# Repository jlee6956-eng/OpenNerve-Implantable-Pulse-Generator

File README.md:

# OpenNerve-Implantable-Pulse-Generator
Source files for the OpenNerve implantable pulse generator (IPG), charger, and user interface software

## Overview

The OpenNerve IPG is designed to enable researchers to develop novel therapies in the neuromodulation and bioelectronic medicine spaces. It is currently being used by a number of groups for acute and chronic preclinical studies, with plan to transition to clinical studies when ready.The IPG is capable of providing current-based bipolar electrical stimulation, measuring biosignals using multiple analog front ends (AFEs), and connecting with third-party sensors via an in-body I2C network. It communicates with a user controller over Bluetooth Low Energy (BLE) and can be easily configured to be rechargeable over inductive link. All source files are released under the CC-BY 4.0 open source copyright license, which requires attribution but allows their use for closed-source and commercial applications.

## Electronics
Two versions of the printed circuit board inside OpenNerve have been designed and manufactured. The [Gen1 PCBA](https://github.com/CARSSCenter/OpenNerve-Implantable-Pulse-Generator/Gen1%20PCBA) has eight pseudo-independent monopolar stimulation channels (configurable as four bipolar channels), two differential biosignal amplifiers for recording ECG, EMG, or eCAPS, and an I2C port for connection to an accelerometer or other in-body digital sensors. The [Gen2 PCBA](https://github.com/CARSSCenter/OpenNerve-Implantable-Pulse-Generator/tree/main/Gen2%20PCBA) has two fully independent bipolar stimulation channels capable of square wave stimulation up to 1200 Hz or low frequency sine wave stimulation, four configurable analog front ends, and an I2C port. See below for electrical specifications for the Gen2 IPG (square wave stimulation and analog front-ends).

## Firmware
OpenNerve contains two microcontrollers: an nRF52810 which controlls BLE communication (referred to as "BLE"), and an STM32 which controls most other functions (referred to as "MCU"). BLE firmware is the same for both Gen1 and Gen2 PCBAs and can be found [here](https://github.com/CARSSCenter/OpenNerve-Implantable-Pulse-Generator/tree/main/FW-BLE). Instructions for programming a new board can be found in the [BLE Flashing Guide](https://github.com/CARSSCenter/OpenNerve-Implantable-Pulse-Generator/blob/main/Docs/BLE-Flashing-Guide.md) under Docs. MCU firmware is different for Gen1 and Gen2 IPGs; the source code and hex files for each board's MCU firmware can be found in their respective folders, and instructions for compiling and flashing can be found at [MCU Flashing Guide](https://github.com/CARSSCenter/OpenNerve-Implantable-Pulse-Generator/blob/main/Docs/MCU-Flashing-Guide.md).

## Software
A Windows application has been written in VSCode to control OpenNerve's functions and download/save measurements. The source code for this app can be found in the [OpenNerve Windows App repo](https://github.com/CARSSCenter/OpenNerve-Windows-App). To communicate with OpenNerve using this app requires an encryption private key. To get the key used for the open-source builds of MCU2 firmware please reach out to carss@usc.edu. There are also instructions included [here](https://github.com/CARSSCenter/OpenNerve-Windows-App/blob/main/encryption-instructions.md) on how to create your own encryption keys and firmware build.

An Android app is also under development for communication and control with OpenNerve. Prototype code for this app can be found [here](https://github.com/CARSSCenter/OpenNerve-Android-App).

## Wireless charger
The OpenNerve IPG can be charged inductively using the [OpenNerve Charger](https://github.com/CARSSCenter/OpenNerve-Charger).

## Contributors
The OpenNerve IPG has been designed and manufactured in partnership with a number of contributors from the academic and private sectors, all of whom are committed to open source neurotech and lowering the barrier to developing new therapies. See below for a list of contributing organizations (last updated 22/01/2026).
* [Biomedical Microsystems Lab, University of Southern California](https://biomems.usc.edu/) - lead the larger CARSS center, set up and maintains open source resources, performs integration testing, software development, and preclinical studies
* [Med-Ally LLC](https://med-ally.com/) - designed the hermetic enclosure for OpenNerve, and provides final assembly services for chronic studies
* [Medipace Inc](https://www.medipaceinc.com/) - Manages electronics and firmware development, performs software development
* [Focus Uy](https://focus.uy/) - Designed the printed circuit board for OpenNerve IPG and charger
* [CoForce Ltd.](https://www.coforcemed.com/) - Peformed firmware development for OpenNerve
* [Veronica Rosado.](https://www.linkedin.com/in/veronica-rosado-silva/) - Developed Sine Wave Generator tool for OpenNerve
* [Julian Lee](https://www.linkedin.com/in/julian-lee-t/) - Worked on sine wave generator

Funding for OpenNerve has been provided by the US National Institutes of Health's SPARC program # [1U41NS129514](https://reporter.nih.gov/project-details/10557000) as well as by the US National Science Foundation's POSE Phase 1 program # [2449357](https://www.nsf.gov/awardsearch/show-award?AWD_ID=2449357). 

# Disclaimer

The contents of this repository are subject to revision. No representation or warranty, express or implied, is provided in relation to the accuracy, correctness, completeness, or reliability of the information, opinions, or conclusions expressed in this repository.

The contents of this repository (the “Materials”) are experimental in nature and should be used with prudence and appropriate caution. Any use is voluntary and at your own risk.

The Materials are made available “as is” by USC (the University of Southern California and its trustees, directors, officers, employees, faculty, students, agents, affiliated organizations and their insurance carriers, if any), its collaborators Med-Ally LLC and Medipace Inc., and any other contributors to this repository (collectively, “Providers”). Providers expressly disclaim all warranties, express or implied, arising in connection with the Materials, or arising out of a course of performance, dealing, or trade usage, including, without limitation, any warranties of title, noninfringement, merchantability, or fitness for a particular purpose.

Any user of the Materials agrees to forever indemnify, defend, and hold harmless Providers from and against, and to waive any and all claims against Providers for any and all claims, suits, demands, liability, loss or damage whatsoever, including attorneys' fees, whether direct or consequential, on account of any loss, injury, death or damage to any person or (including without limitation all agents and employees of Providers and all property owned by, leased to or used by either Providers) or on account of any loss or damages to business or reputations or privacy of any persons, arising in whole or in part in any way from use of the Materials or in any way connected therewith or in any way related thereto.

The Materials, any related materials, and all intellectual property therein, are owned by Providers.

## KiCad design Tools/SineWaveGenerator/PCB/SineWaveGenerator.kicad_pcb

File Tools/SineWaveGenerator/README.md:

# SineWaveGeneratorDev
Development for sine wave generator

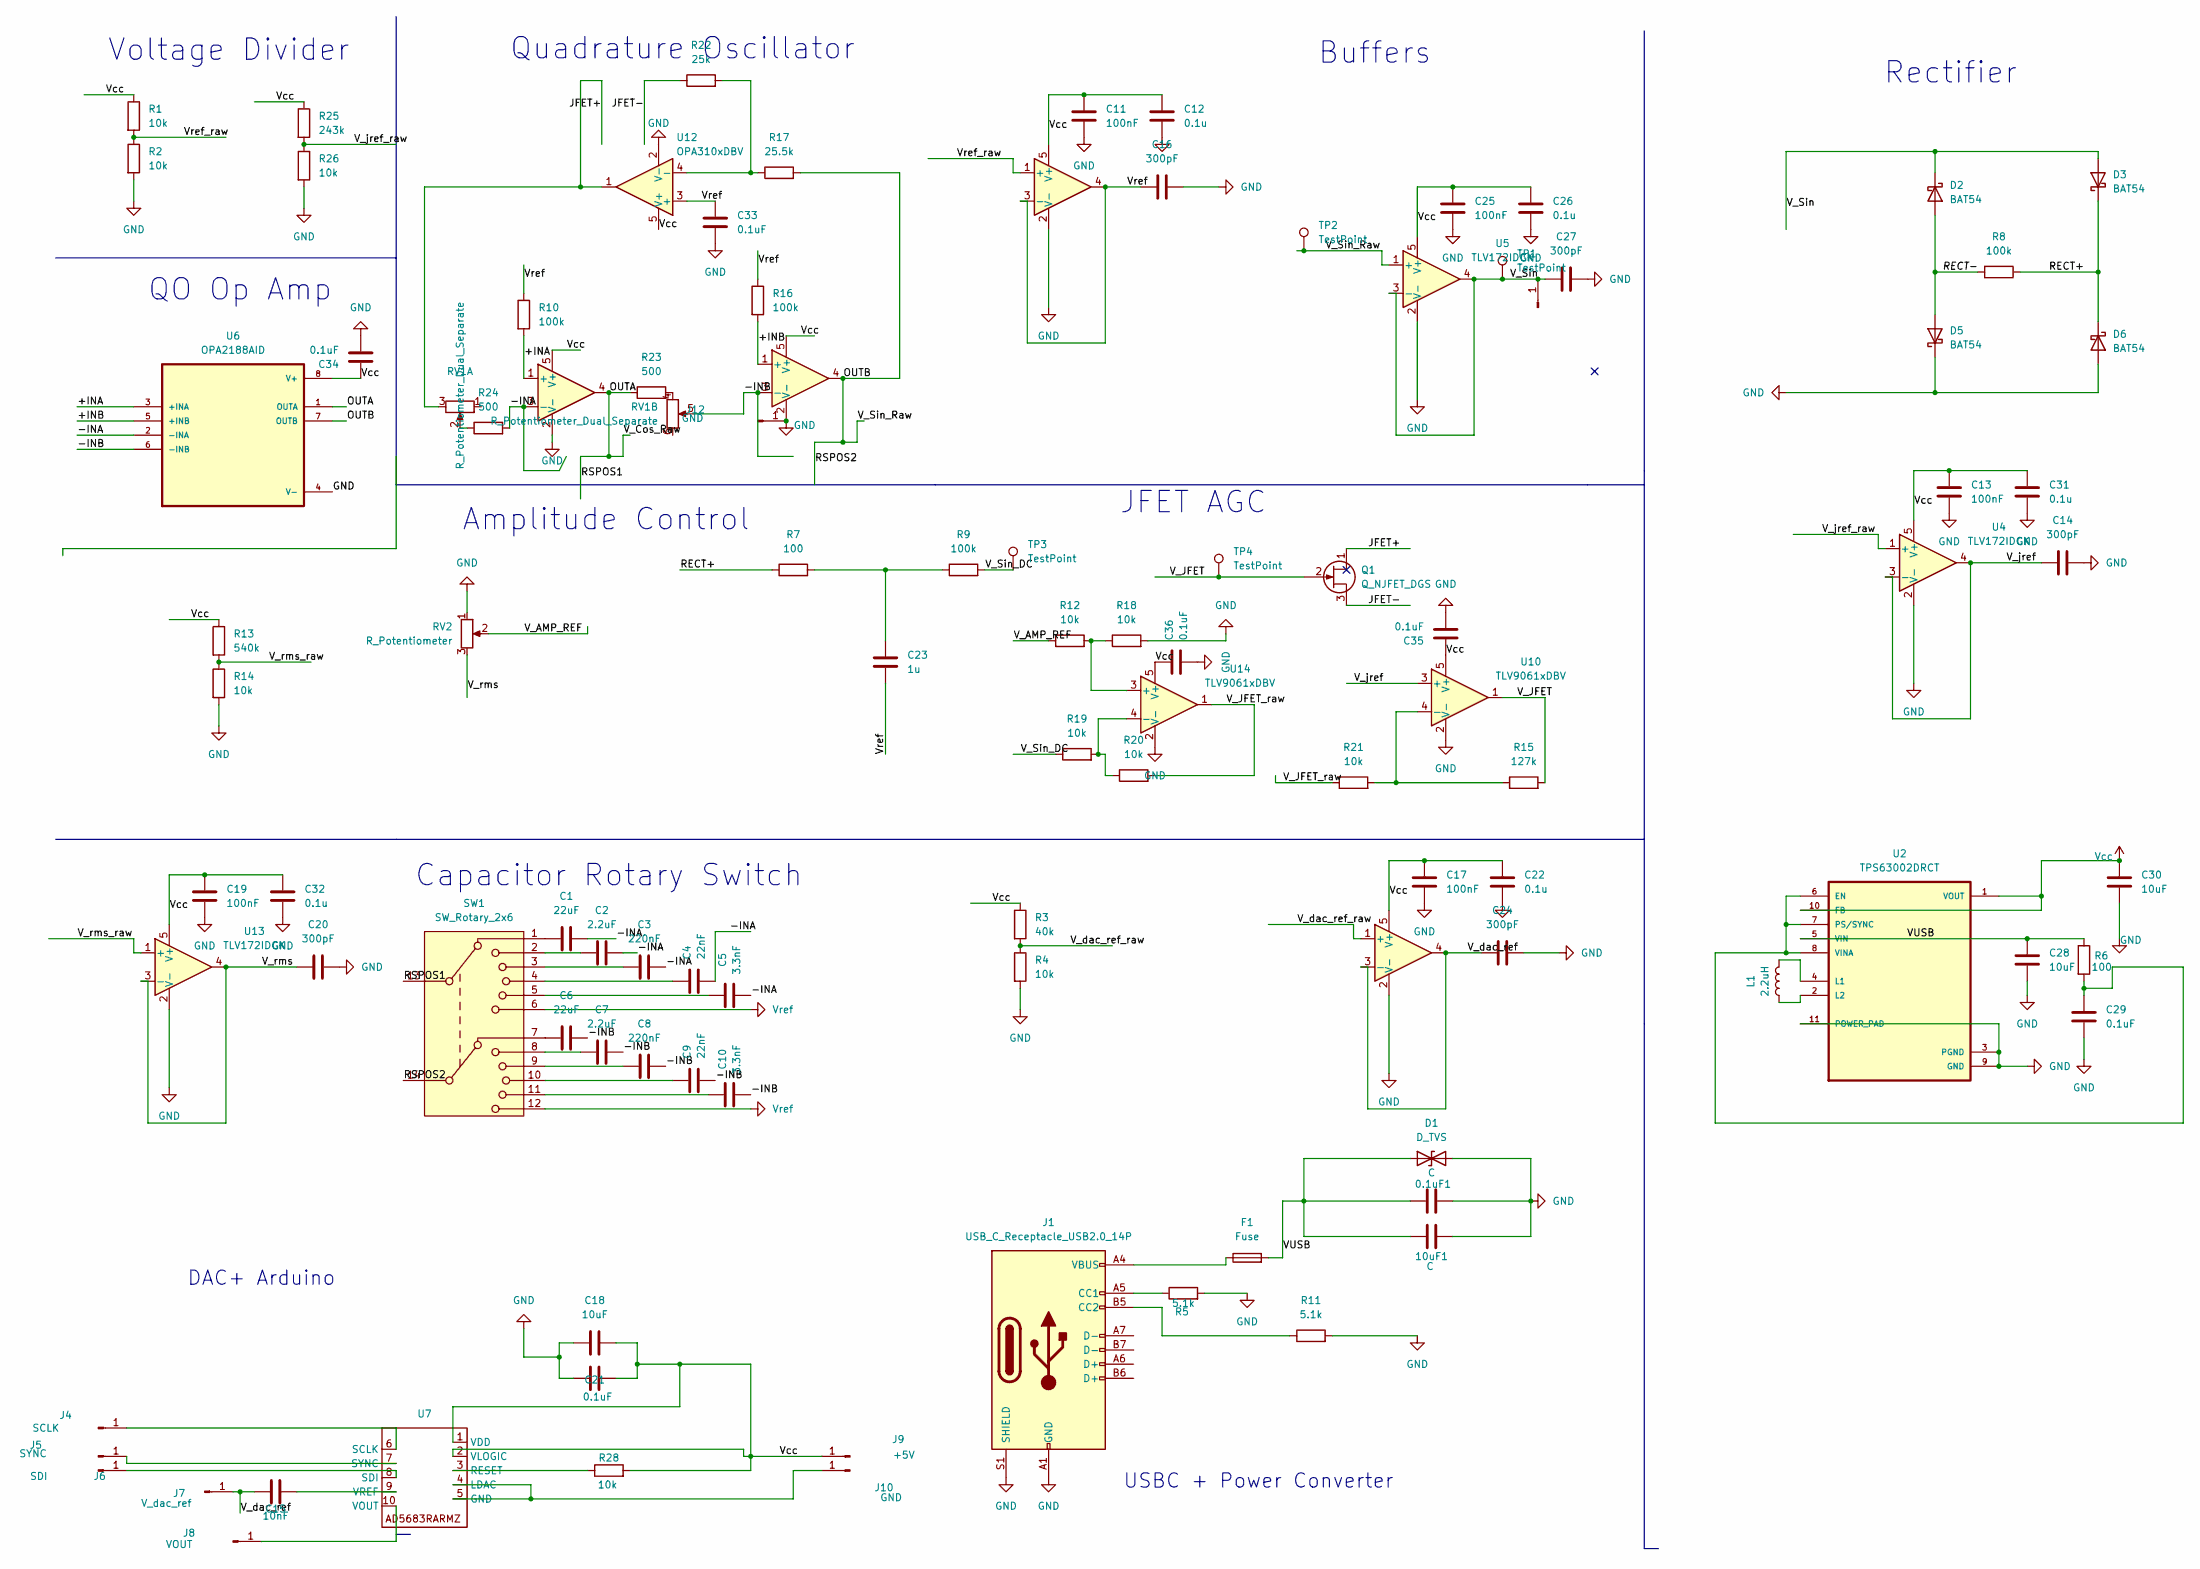
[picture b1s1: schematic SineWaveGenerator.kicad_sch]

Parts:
0.1uF1, 10uF1: C; C_0805_2012Metric_Pad1.18x1.45mm_HandSolder
C1, C6: 22uF; C_0805_2012Metric_Pad1.18x1.45mm_HandSolder
C2, C7: 2.2uF; C_0805_2012Metric_Pad1.18x1.45mm_HandSolder
C3, C8: 220nF; C_0805_2012Metric_Pad1.18x1.45mm_HandSolder
C4, C9: 22nF; C_0805_2012Metric_Pad1.18x1.45mm_HandSolder
C5, C10: 3.3nF; C_0805_2012Metric_Pad1.18x1.45mm_HandSolder
C11, C13, C17, C19, C25: 100nF; C_0805_2012Metric_Pad1.18x1.45mm_HandSolder
C12, C22, C26, C31, C32: 0.1u; C_0805_2012Metric_Pad1.18x1.45mm_HandSolder
C14, C16, C20, C24, C27: 300pF; C_0805_2012Metric_Pad1.18x1.45mm_HandSolder
C15: 10nF; C_0805_2012Metric_Pad1.18x1.45mm_HandSolder
C18, C28, C30: 10uF; C_0805_2012Metric_Pad1.18x1.45mm_HandSolder
C21, C29, C33, C34, C35, C36: 0.1uF; C_0805_2012Metric_Pad1.18x1.45mm_HandSolder
C23: 1u; C_0603_1608Metric_Pad1.08x0.95mm_HandSolder
D1: D_TVS; D_SOD-323_HandSoldering
D2, D3, D5, D6: BAT54; D_0805_2012Metric_Pad1.15x1.40mm_HandSolder
F1: Fuse; Fuse_0805_2012Metric
J1: USB_C_Receptacle_USB2.0_14P; USB_C_Receptacle_HRO_TYPE-C-31-M-12
J4: SCLK; PinHeader_1x01_P2.54mm_Vertical
J5: SYNC; PinHeader_1x01_P2.54mm_Vertical
J6: SDI; PinHeader_1x01_P2.54mm_Vertical
J7: V_dac_ref; PinHeader_1x01_P2.54mm_Vertical
J8: VOUT; PinHeader_1x01_P2.54mm_Vertical
J9: +5V; PinHeader_1x01_P2.54mm_Vertical
J10, J12: GND; PinHeader_1x01_P2.54mm_Vertical
J11: Out_Sin; PinHeader_1x01_P2.54mm_Vertical
L1: 2.2uH; L_Coilcraft_LPS3010
Q1: Q_NJFET_DGS; TRANS_J201
R1, R2, R4, R12, R14, R18, R19, R20, R21, R26, R28: 10k; R_0805_2012Metric_Pad1.20x1.40mm_HandSolder
R3: 40k; R_0805_2012Metric_Pad1.20x1.40mm_HandSolder
R5, R11: 5.1k; R_0805_2012Metric_Pad1.20x1.40mm_HandSolder
R6, R7: 100; R_0805_2012Metric_Pad1.20x1.40mm_HandSolder
R8, R9, R10, R16: 100k; R_0805_2012Metric_Pad1.20x1.40mm_HandSolder
R13: 540k; R_0805_2012Metric_Pad1.20x1.40mm_HandSolder
R15: 127k; R_0805_2012Metric_Pad1.20x1.40mm_HandSolder
R17: 25.5k; R_0805_2012Metric_Pad1.20x1.40mm_HandSolder
R22: 25k; R_0805_2012Metric_Pad1.20x1.40mm_HandSolder
R23, R24: 500; R_0805_2012Metric_Pad1.20x1.40mm_HandSolder
R25: 243k; R_0805_2012Metric_Pad1.20x1.40mm_HandSolder
RV1: R_Potentiometer_Dual_Separate; DUALGANG_fixed
RV2: R_Potentiometer; BOURNS_POT
SW1: SW_Rotary_2x6; SW_CK1050
TP1, TP2, TP3, TP4: TestPoint; TestPoint_Pad_D1.0mm
U2: TPS63002DRCT; VREG_V62_16624-01YE
U4, U5, U8, U11, U13, U15, U16: TLV172IDCK; SOT-353_SC-70-5
U6: OPA2188AID; SOIC127P599X175-8N
U7: MSOP-10_3x3mm_P0.5mm
U10, U14: TLV9061xDBV; SOT-23-5
U12: OPA310xDBV; SOT-23-5

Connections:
/+INA: R10.2, U6.3 (+INA), U8.1 (+)
/+INB: R16.2, U6.5 (+INB), U11.1 (+)
/-INA: C1.2, C2.2, C3.2, C4.2, C5.2, R24.2, U6.2 (-INA), U8.3 (-)
/-INB: C6.2, C7.2, C8.2, C9.2, C10.2, RV1.5, U6.6 (-INB), U11.3 (-)
/JFET+: Q1.1 (D), RV1.3, U12.1
/JFET-: Q1.3 (S), R22.1
/OUTA: R23.1, SW1.13, U6.1 (OUTA), U8.4
/OUTB: R17.2, SW1.14, TP2.1 (1_1), U5.1 (+), U6.7 (OUTB), U11.4
/RECT+: D3.1 (K), D6.1 (K), R7.1, R8.1
/RECT-: D2.2 (A), D5.2 (A), R8.2
/VUSB: 0.1uF1.1, 10uF1.1, C28.1, D1.1 (A1), F1.2, R6.1, U2.5 (VIN)
/V_AMP_REF: R12.1, RV2.2
/V_JFET: Q1.2 (G), R15.2, TP4.1 (1_1), U10.1
/V_JFET_raw: R20.2, R21.1, U14.1
/V_Sin: C27.1, D2.1 (K), D3.2 (A), J11.1 (Pin_1_1), TP1.1 (1_1), U5.3 (-), U5.4
/V_Sin_DC: R9.2, R19.1, TP3.1 (1_1)
/V_dac_ref: C15.1, C24.1, J7.1 (Pin_1_1), U16.3 (-), U16.4
/V_dac_ref_raw: R3.2, R4.1, U16.1 (+)
/V_jref: C14.1, U4.3 (-), U4.4, U10.3 (+)
/V_jref_raw: R25.2, R26.1, U4.1 (+)
/V_rms: C20.1, RV2.3, U13.3 (-), U13.4
/V_rms_raw: R13.2, R14.1, U13.1 (+)
/Vref_raw: R1.2, R2.1, U15.1 (+)
GND: 0.1uF1.2, 10uF1.2, C11.2, C12.2, C13.1, C14.2, C16.2, C17.2, C18.1, C19.1, C20.2, C21.1, C22.2, C24.2, C25.1, C26.2, C27.2, C28.2, C29.2, C30.2, C31.2, C32.2, C33.2, C34.2, C35.2, C36.2, D1.2 (A2), D5.1 (K), D6.2 (A), J1.A1 (GND), J1.A12 (GND), J1.B1 (GND), J1.B12 (GND), J1.S1 (SHIELD), J1.SH, J12.1 (Pin_1_1), R2.2, R4.2, R5.2, R11.2, R14.2, R18.2, R26.2, RV2.1, U2.3 (PGND), U2.9 (GND), U2.11 (POWER_PAD), U2.12, U2.13, U2.14, U2.15, U4.2 (V-), U5.2 (V-), U6.4 (V-), U8.2 (V-), U10.2 (V-), U11.2 (V-), U12.2 (V-), U13.2 (V-), U14.2 (V-), U15.2 (V-), U16.2 (V-)
unnamed: C1.1, SW1.1
unnamed: C2.1, SW1.2
unnamed: C3.1, SW1.3
unnamed: C4.1, SW1.4
unnamed: C5.1, SW1.5
unnamed: C6.1, SW1.7
unnamed: C7.1, SW1.8
unnamed: C8.1, SW1.9
unnamed: C9.1, SW1.10
unnamed: C10.1, SW1.11
unnamed: C23.1, R7.2, R9.1
unnamed: F1.1, J1.A4 (VBUS), J1.A9 (VBUS), J1.B4 (VBUS), J1.B9 (VBUS)
unnamed: J1.A5 (CC1), R5.1
unnamed: J1.B5 (CC2), R11.1
unnamed: J4.1 (Pin_1_1), U7.6 (SCLK)
unnamed: J5.1 (Pin_1_1), U7.7 (SYNC)
unnamed: J6.1 (Pin_1_1), U7.8 (SDI)
unnamed: J8.1 (Pin_1_1), U7.10 (VOUT)
unnamed: J10.1 (Pin_1_1), U7.4 (LDAC), U7.5 (GND)
unnamed: R23.2, RV1.4
unnamed: R24.1, RV1.2
unnamed: C29.1, R6.2, U2.6 (EN), U2.7 (PS/SYNC), U2.8 (VINA)
unnamed: L1.2, U2.4 (L1)
unnamed: L1.1, U2.2 (L2)
unnamed: R28.1, U7.3 (RESET)
unnamed: C15.2, U7.9 (VREF)
unnamed: R15.1, R21.2, U10.4 (-)
unnamed: R17.1, R22.2, U12.4 (-)
unnamed: R12.2, R18.1, U14.3 (+)
unnamed: R19.2, R20.1, U14.4 (-)
Vcc: C11.1, C12.1, C13.2, C17.1, C18.2, C19.2, C21.2, C22.1, C25.2, C26.1, C30.1, C31.1, C32.1, C34.1, C35.1, C36.1, J9.1 (Pin_1_1), R1.1, R3.1, R13.1, R25.1, R28.2, U2.1 (VOUT), U2.10 (FB), U4.5 (V+), U5.5 (V+), U6.8 (V+), U7.1 (VDD), U7.2 (VLOGIC), U8.5 (V+), U10.5 (V+), U11.5 (V+), U12.5 (V+), U13.5 (V+), U14.5 (V+), U15.5 (V+), U16.5 (V+)
Vref: C16.1, C23.2, C33.1, R10.1, R16.1, SW1.6, SW1.12, U12.3 (+), U15.3 (-), U15.4

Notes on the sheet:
Rectifier
Quadrature Oscillator
DAC+ Arduino
Buffers
QO Op Amp
Amplitude Control
Capacitor Rotary Switch
JFET AGC
USBC + Power Converter
Voltage Divider

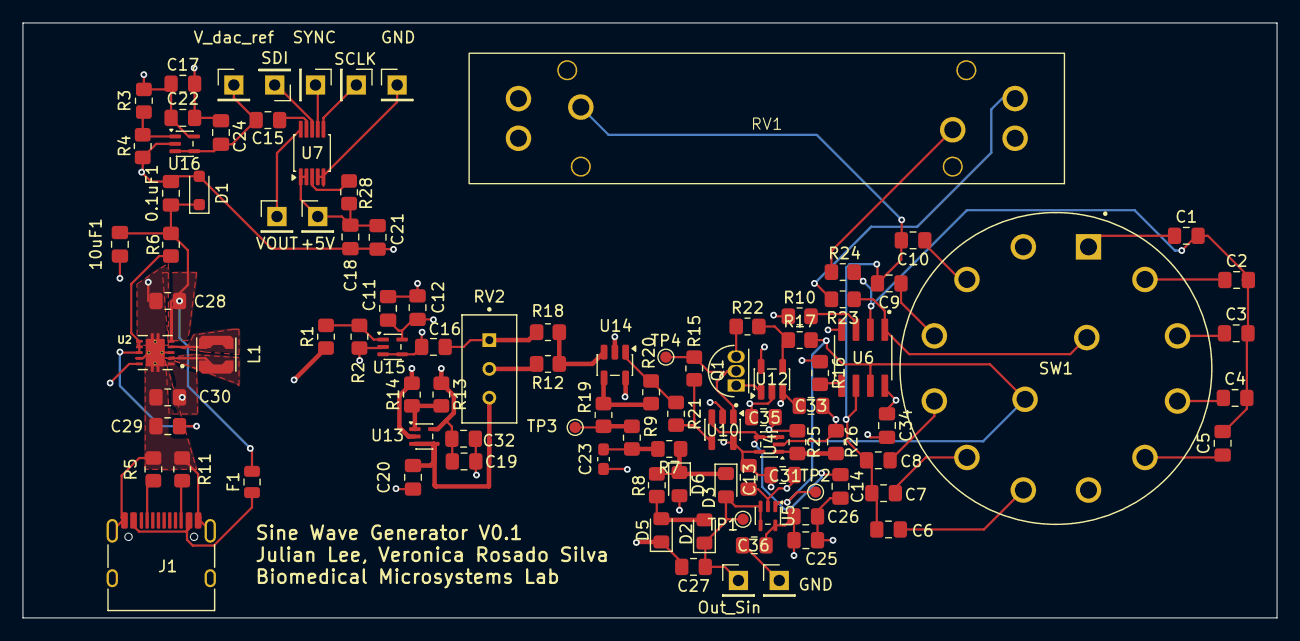
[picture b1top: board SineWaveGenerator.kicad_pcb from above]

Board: 4 copper layers, 110.6 x 52.5 mm, 101 parts (0 on the bottom side), 56 nets.

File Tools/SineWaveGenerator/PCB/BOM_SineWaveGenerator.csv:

"Reference","Qty","Value","DNP","Exclude from BOM","Exclude from Board","Footprint","Description"
"0.1uF1,10uF1","2","C","","","","Capacitor_SMD:C_0805_2012Metric_Pad1.18x1.45mm_HandSolder","Unpolarized capacitor"
"C1,C6","2","22uF","","","","Capacitor_SMD:C_0805_2012Metric_Pad1.18x1.45mm_HandSolder","Unpolarized capacitor"
"C2,C7","2","2.2uF","","","","Capacitor_SMD:C_0805_2012Metric_Pad1.18x1.45mm_HandSolder","Unpolarized capacitor"
"C3,C8","2","220nF","","","","Capacitor_SMD:C_0805_2012Metric_Pad1.18x1.45mm_HandSolder","Unpolarized capacitor"
"C4,C9","2","22nF","","","","Capacitor_SMD:C_0805_2012Metric_Pad1.18x1.45mm_HandSolder","Unpolarized capacitor"
"C5,C10","2","3.3nF","","","","Capacitor_SMD:C_0805_2012Metric_Pad1.18x1.45mm_HandSolder","Unpolarized capacitor"
"C11,C13,C17,C19,C25","5","100nF","","","","Capacitor_SMD:C_0805_2012Metric_Pad1.18x1.45mm_HandSolder","Unpolarized capacitor"
"C12,C22,C26,C31,C32","5","0.1u","","","","Capacitor_SMD:C_0805_2012Metric_Pad1.18x1.45mm_HandSolder","Unpolarized capacitor"
"C14,C16,C20,C24,C27","5","300pF","","","","Capacitor_SMD:C_0805_2012Metric_Pad1.18x1.45mm_HandSolder","Unpolarized capacitor"
"C15","1","10nF","","","","Capacitor_SMD:C_0805_2012Metric_Pad1.18x1.45mm_HandSolder","Unpolarized capacitor"
"C18,C28,C30","3","10uF","","","","Capacitor_SMD:C_0805_2012Metric_Pad1.18x1.45mm_HandSolder","Unpolarized capacitor"
"C21,C29,C33,C34,C35,C36","6","0.1uF","","","","Capacitor_SMD:C_0805_2012Metric_Pad1.18x1.45mm_HandSolder","Unpolarized capacitor"
"C23","1","1u","","","","Capacitor_SMD:C_0603_1608Metric_Pad1.08x0.95mm_HandSolder","Unpolarized capacitor"
"D1","1","D_TVS","","","","Diode_SMD:D_SOD-323_HandSoldering","Bidirectional transient-voltage-suppression diode"
"D2,D3,D5,D6","4","BAT54","","","","Diode_SMD:D_0805_2012Metric_Pad1.15x1.40mm_HandSolder","Schottky diode"
"F1","1","Fuse","","","","Fuse:Fuse_0805_2012Metric","Fuse"
"J1","1","USB_C_Receptacle_USB2.0_14P","","","","Connector_USB:USB_C_Receptacle_HRO_TYPE-C-31-M-12","USB 2.0-only 14P Type-C Receptacle connector"
"J4","1","SCLK","","","","Connector_PinHeader_2.54mm:PinHeader_1x01_P2.54mm_Vertical","Generic connector, single row, 01x01, script generated"
"J5","1","SYNC","","","","Connector_PinHeader_2.54mm:PinHeader_1x01_P2.54mm_Vertical","Generic connector, single row, 01x01, script generated"
"J6","1","SDI","","","","Connector_PinHeader_2.54mm:PinHeader_1x01_P2.54mm_Vertical","Generic connector, single row, 01x01, script generated"
"J7","1","V_dac_ref","","","","Connector_PinHeader_2.54mm:PinHeader_1x01_P2.54mm_Vertical","Generic connector, single row, 01x01, script generated"
"J8","1","VOUT","","","","Connector_PinHeader_2.54mm:PinHeader_1x01_P2.54mm_Vertical","Generic connector, single row, 01x01, script generated"
"J9","1","+5V","","","","Connector_PinHeader_2.54mm:PinHeader_1x01_P2.54mm_Vertical","Generic connector, single row, 01x01, script generated"
"J10,J12","2","GND","","","","Connector_PinHeader_2.54mm:PinHeader_1x01_P2.54mm_Vertical","Generic connector, single row, 01x01, script generated"
"J11","1","Out_Sin","","","","Connector_PinHeader_2.54mm:PinHeader_1x01_P2.54mm_Vertical","Generic connector, single row, 01x01, script generated"
"L1","1","2.2uH","","","","Inductor_SMD:L_Coilcraft_LPS3010","Inductor"
"Q1","1","Q_NJFET_DGS","","","","JFET:TRANS_J201","N-JFET transistor, drain/gate/source"
"R1,R2,R4,R12,R14,R18,R19,R20,R21,R26,R28","11","10k","","","","Resistor_SMD:R_0805_2012Metric_Pad1.20x1.40mm_HandSolder","Resistor"
"R3","1","40k","","","","Resistor_SMD:R_0805_2012Metric_Pad1.20x1.40mm_HandSolder","Resistor"
"R5,R11","2","5.1k","","","","Resistor_SMD:R_0805_2012Metric_Pad1.20x1.40mm_HandSolder","Resistor"
"R6,R7","2","100","","","","Resistor_SMD:R_0805_2012Metric_Pad1.20x1.40mm_HandSolder","Resistor"
"R8,R9,R10,R16","4","100k","","","","Resistor_SMD:R_0805_2012Metric_Pad1.20x1.40mm_HandSolder","Resistor"
"R13","1","540k","","","","Resistor_SMD:R_0805_2012Metric_Pad1.20x1.40mm_HandSolder","Resistor"
"R15","1","127k","","","","Resistor_SMD:R_0805_2012Metric_Pad1.20x1.40mm_HandSolder","Resistor"
"R17","1","25.5k","","","","Resistor_SMD:R_0805_2012Metric_Pad1.20x1.40mm_HandSolder","Resistor"
"R22","1","25k","","","","Resistor_SMD:R_0805_2012Metric_Pad1.20x1.40mm_HandSolder","Resistor"
"R23,R24","2","500","","","","Resistor_SMD:R_0805_2012Metric_Pad1.20x1.40mm_HandSolder","Resistor"
"R25","1","243k","","","","Resistor_SMD:R_0805_2012Metric_Pad1.20x1.40mm_HandSolder","Resistor"
"RV1","1","R_Potentiometer_Dual_Separate","","","","Potentiometer_THT:DUALGANG_fixed","Dual potentiometer, separate units"
"RV2","1","R_Potentiometer","","","","Potentiometer_THT:BOURNS_POT","Potentiometer"
"SW1","1","SW_Rotary_2x6","","","","Rotary_Encoder:SW_CK1050","2 rotary switch with 6 positions"
"TP1,TP2,TP3,TP4","4","TestPoint","","","","TestPoint:TestPoint_Pad_D1.0mm","test point"
"U2","1","TPS63002DRCT","","","","JFET:VREG_V62_16624-01YE","96% Buck-Boost Converter with 1.7A Current Switches, 5V fixed Output voltage in 3x3 QFN"
"U4,U5,U13,U15,U16","5","TLV172IDCK","","","","Package_TO_SOT_SMD:SOT-353_SC-70-5","Low-power Operational Amplifier, SOT-353"
"U6","1","OPA2188AID","","","","OPA2188AID:SOIC127P599X175-8N","0.03µV/°C, 6µV Vos, Low Noise, Rail-to-Rail Output, 36V Zero-Drift Operational Amplifier"
"U7","1","","","","","Package_SO:MSOP-10_3x3mm_P0.5mm",""
"U10,U14","2","TLV9061xDBV","","","","Package_TO_SOT_SMD:SOT-23-5","10-MHz, RRIO, CMOS Operational Amplifiers for Cost-Sensitive Systems, SOT-23-5"
"U12","1","OPA310xDBV","","","","Package_TO_SOT_SMD:SOT-23-5","High output current, Rail-to-Rail Input/Output, 3MHz GBW, Operational Amplifiers, integrated RFI/EMI filter, 1.5V to 5.5V supply, SOT-23-5"
